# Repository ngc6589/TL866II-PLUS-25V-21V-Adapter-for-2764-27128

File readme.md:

# TL866II PLUS 25V/21V アダプター for 2764/17128

## 概要
当アダプタは XGecu TL866II PLUS プログラマにて 2764/27128 UV-EPROM 書き込みのための 25V/21V を供給するサポートアダプターです。TL866II PLUS の書き込み電圧 18V を検出すると ROM の VPP ピンに 25V/21V を供給します。25V/21V の電圧は  9～12V の ACアダプタから供給された電圧を昇圧ICで 25V/21V にします。

基板は https://www.em9system.com/?p=989 にて頒布いたします。

## 部品表
本来は部品の種類別にソートするものですが、購入先別に分けて記載しています。

|部品番号|部品名|URL|数量|備考|
|----|----|----|----|----|
|U1|DCDCコンバーター制御用IC NJM2360AD|https://akizukidenshi.com/catalog/g/gI-12365/|1|MC34063A も使えます|
|U1|丸ピンICソケット ( 8P)|https://akizukidenshi.com/catalog/g/gP-00035/|1|
|Q1|トランジスタ 2SA733L-K-T92-K 60V150mA|https://akizukidenshi.com/catalog/g/gI-11427/|1|TO-92ECB 手持ちの 2SA1015 などもOK|
|Q2|トランジスタ 2SC945L-K-T92-K 60V150mA|https://akizukidenshi.com/catalog/g/gI-11428/|1|TO-92ECB 手持ちの 2SC1815 などもOK|
|D1,D3|ショットキーバリアダイオード 40V1A 11EQS04|https://akizukidenshi.com/catalog/g/gI-11363/|2|
|D2|定電圧ダイオード(ツェナーダイオード) 15V500mW GDZJ15C|https://akizukidenshi.com/catalog/g/gI-07498/|1|DO-34|
|C5|メタライズドポリエステルフィルムコンデンサ 1500pF100V|https://akizukidenshi.com/catalog/g/gP-14588/|1||7.5mm×6.5mm×2.5mm ピッチ5mm|
|L1|インダクター 220μH0.75A SRC1013|https://akizukidenshi.com/catalog/g/gP-16012/|1|11x12.5 ピッチ5mm|
|J1|2.1mm標準DCジャック(4A) 基板取付用 MJ-179PH|https://akizukidenshi.com/catalog/g/gC-06568/|1|
|J2|細ピンヘッダ 1×40 (黒)|https://akizukidenshi.com/catalog/g/gC-06631/|1|
|J3|ゼロプレッシャーICソケット 28P 600mil|https://akizukidenshi.com/catalog/g/gP-11743/|1|
|JP1|ジャンパーピン赤(2.54mmピッチ)(25個入)|https://akizukidenshi.com/catalog/g/gP-03688/|1|
|R1|小形金属皮膜抵抗(MOSX)2W 0.22Ω【MOSX2CR22J】 |https://www.marutsu.co.jp/pc/i/18085/|1|L=15mm D=4mm|
|R2|【MOS2C181J】小型酸金抵抗(MOS)2W 180Ω|https://www.marutsu.co.jp/pc/i/18155/|1|L=15mm D=4mm|
|R3|1/4W金属皮膜抵抗 4.7kΩ 黄紫黒茶茶【MF1/4CC4701F】 |https://www.marutsu.co.jp/pc/i/1313/|1|L=7.1mm D=2.3mm|
|R4|1/4W金属皮膜抵抗 24kΩ 赤黄黒赤茶【MF1/4CC2402F】 |https://www.marutsu.co.jp/pc/i/1283/|1|L=7.1mm D=2.3mm|
|R5|1/4W金属皮膜抵抗 1.5kΩ 茶緑黒茶茶【MF1/4CC1501F】|https://www.marutsu.co.jp/pc/i/1248/|1|L=7.1mm D=2.3mm|
|R6,R8,R9|1/4W金属皮膜抵抗 1kΩ 茶黒黒茶茶【MF1/4CC1001F】|https://www.marutsu.co.jp/pc/i/1263/|3|L=7.1mm D=2.3mm|
|R7|1/4W金属皮膜抵抗 12kΩ 茶赤黒赤茶【MF1/4CC1202F】|https://www.marutsu.co.jp/pc/i/1253/|1|L=7.1mm D=2.3mm|
|R10|1/4W金属皮膜抵抗 10kΩ 茶黒黒赤茶【MF1/4CC1002F】|https://www.marutsu.co.jp/pc/i/1251/|1|L=7.1mm D=2.3mm|
|C1,C3|【RDER71H104K0K1H03B】セラミックコンデンサ 0.1UF 50V X7R ラジアル|https://www.marutsu.co.jp/pc/i/834991/|2|4mmx2.5mm ピッチ5mm|
|C2|小形アルミニウム電解コンデンサー25V 100μF【25PK100MEFC】|https://www.marutsu.co.jp/pc/i/132144/|1|D=5mm ピッチ2mm|
|C4|小形アルミニウム電解コンデンサー50V 330μF【50PK330MEFC】|https://www.marutsu.co.jp/pc/i/132162/|1|D=10 ピッチ5mm|
|JP1|2ピン基板用ピンヘッダー[2ピン×1列]【2130S1*2GSE】 |https://www.marutsu.co.jp/pc/i/590531/|1|
||プリント基板||1|頒布品を買われた方は基板製造不要|

- R1, R2 は 2W サイズと大きいものを選定していますが、ROM のプログラミングだけでこのワット数は不要です。しかしながらこの回路を参考にされて電流を取り出す用途に流用された時は、発熱の可能性があるためマージンを取った形にしています。
- Q1, Q2 汎用でいいのですが、秋月だと10個単位とかになってしまうので1個単位で買えるトランジスタを選定しています。
- 1/4W 抵抗のうち、R3, R4, R5 は DC/DC チップの基準電圧用なので金属皮膜 1% を使用して下さい。それ以外の抵抗は 5% カーボンでも問題ありません。これも通販だと 10本/100本単位がほとんどなので1本単位で購入出来るものにしています。

部品表には書いていませんが、9～12V の ACアダプタもご用意ください。

## 回路図
リポジトリにある schematic-nnnnnn.pdf (nnnnnnは日付) を参照下さい。

## ガーバーファイル
リポジトリにある gaeber-nnnnnn.zip (nnnnnnは日付) を参照下さい。

## 組み立て時の注意
**ZIF ソケットをハンダ付けする前に細ピンヘッダを先にハンダ付けしてください。** これ以外は特に取り付け順はありません。

## 書き込み実績
手持ちが少ないですが以下の ROM 書き込み出来ました。
- INTEL D2764D(21V)
- FUJITSU MBM2764-25(21V)
- INTEL D27128-3(21V)
- FUJITSU MBM27128-20(21V)
- MITSUBISHI M5L27128K(21V)

## 書き込み方法
- アダプタを TL866II PLUS のソケットに装着する
- ROM の書き込み電圧に合わせて 25V はジャンパを外す 21V ならジャンパ装着する
- 9 ～ 12V の ACアダプタを挿して電源を供給する
- XGpro アプリケーションを起動しチップの選択をします。
- 画面左下の [Pin Detect] [Check ID] のチェックボックスを外す

- READ ボタンを押してエラーないことを確認
- HEX ファイルを LOAD する
- PROG ボタンを押して書き込む
- 書き込み不調の場合は Pulse Delay を最大 1000us にするといけることがあります。

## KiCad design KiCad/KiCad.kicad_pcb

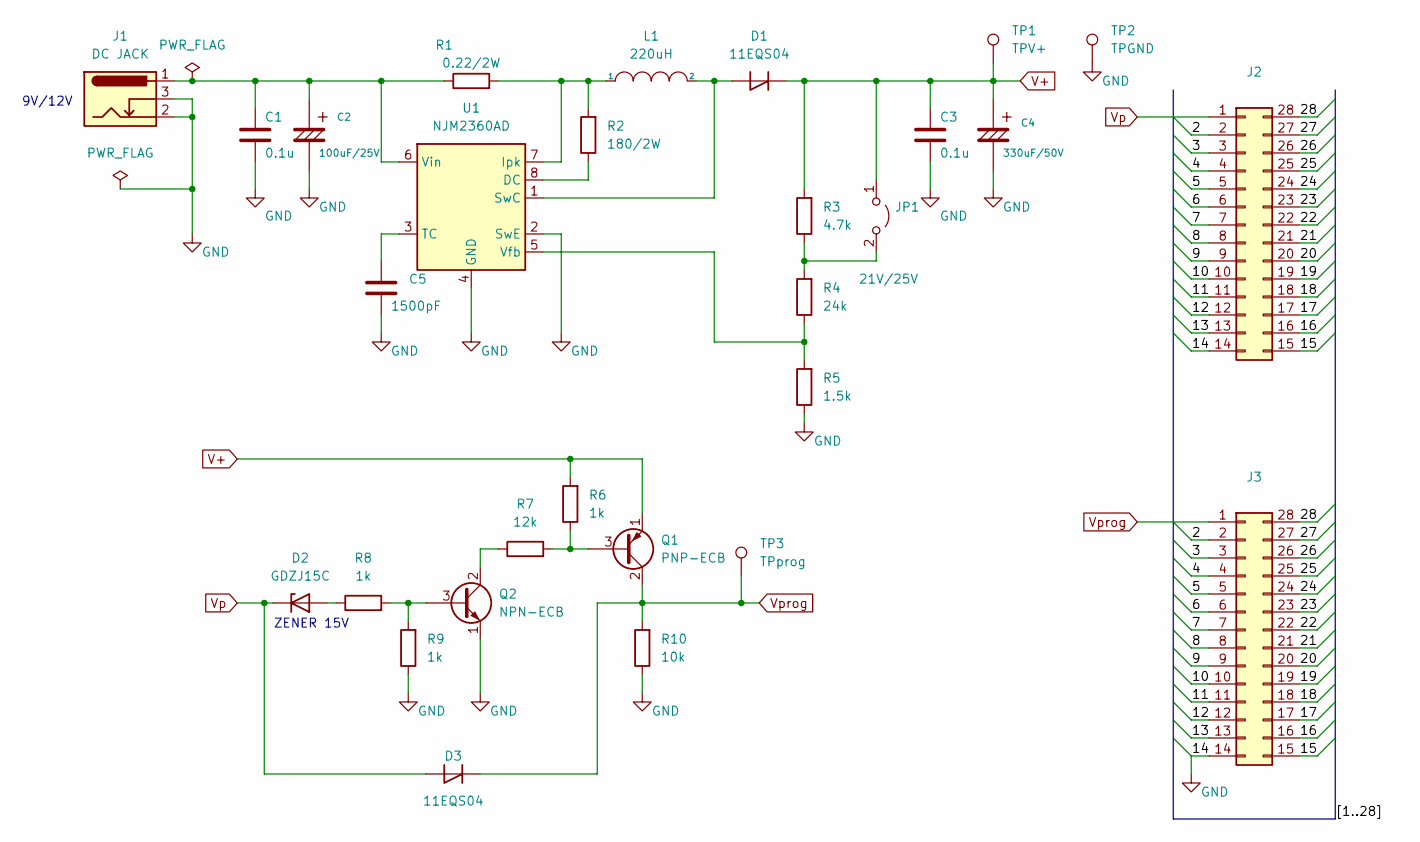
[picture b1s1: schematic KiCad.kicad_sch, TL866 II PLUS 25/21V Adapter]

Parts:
C1, C3: 0.1u; C_Disc_D4.7mm_W2.5mm_P5.00mm
C2: 100uF/25V; CP_Radial_D5.0mm_P2.00mm
C4: 330uF/50V; CP_Radial_D10.0mm_P5.00mm
C5: 1500pF; C_Rect_L7.2mm_W2.5mm_P5.00mm_FKS2_FKP2_MKS2_MKP2
D1, D3: 11EQS04; D_DO-41_SOD81_P10.16mm_Horizontal
D2: GDZJ15C; D_DO-34_SOD68_P7.62mm_Horizontal
J1: DC JACK; MJ-179PH
J2, J3: (no value)
JP1: 21V/25V; PinHeader_1x02_P2.54mm_Vertical
L1: 220uH; L_Radial_D12.0mm_P5.00mm_Fastron_11P
Q1: PNP-ECB; TO-92
Q2: NPN-ECB; TO-92
R1: 0.22/2W; R_Axial_DIN0414_L11.9mm_D4.5mm_P15.24mm_Horizontal
R2: 180/2W; R_Axial_DIN0414_L11.9mm_D4.5mm_P15.24mm_Horizontal
R3: 4.7k; R_Axial_DIN0207_L6.3mm_D2.5mm_P7.62mm_Horizontal
R4: 24k; R_Axial_DIN0207_L6.3mm_D2.5mm_P7.62mm_Horizontal
R5: 1.5k; R_Axial_DIN0207_L6.3mm_D2.5mm_P7.62mm_Horizontal
R6, R8, R9: 1k; R_Axial_DIN0207_L6.3mm_D2.5mm_P7.62mm_Horizontal
R7: 12k; R_Axial_DIN0207_L6.3mm_D2.5mm_P7.62mm_Horizontal
R10: 10k; R_Axial_DIN0207_L6.3mm_D2.5mm_P7.62mm_Horizontal
TP1: TPV+; TestPoint_THTPad_D2.0mm_Drill1.0mm
TP2: TPGND; TestPoint_THTPad_D2.0mm_Drill1.0mm
TP3: TPprog; TestPoint_THTPad_D2.0mm_Drill1.0mm
U1: NJM2360AD; DIP-8_W7.62mm

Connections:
/2: J2.2, J3.2
/3: J2.3, J3.3
/4: J2.4, J3.4
/5: J2.5, J3.5
/6: J2.6, J3.6
/7: J2.7, J3.7
/8: J2.8, J3.8
/9: J2.9, J3.9
/10: J2.10, J3.10
/11: J2.11, J3.11
/12: J2.12, J3.12
/13: J2.13, J3.13
/15: J2.15, J3.15
/16: J2.16, J3.16
/17: J2.17, J3.17
/18: J2.18, J3.18
/19: J2.19, J3.19
/20: J2.20, J3.20
/21: J2.21, J3.21
/22: J2.22, J3.22
/23: J2.23, J3.23
/24: J2.24, J3.24
/25: J2.25, J3.25
/26: J2.26, J3.26
/27: J2.27, J3.27
/28: J2.28, J3.28
GND: C1.2, C2.2, C3.2, C4.2, C5.2, J1.2, J1.3, J2.14, J3.14, Q2.1 (E), R5.1, R9.1, R10.1, TP2.1, U1.2 (SwE), U1.4 (GND)
unnamed: C1.1, C2.1, J1.1, R1.1, U1.6 (Vin)
unnamed: C5.1, U1.3 (TC)
unnamed: D1.2 (A), L1.2, U1.1 (SwC)
unnamed: D2.2 (A), R8.1
unnamed: JP1.2 (B), R3.1, R4.2
unnamed: L1.1, R1.2, R2.2, U1.7 (Ipk)
unnamed: Q1.3 (B), R6.1, R7.2
unnamed: Q2.2 (C), R7.1
unnamed: Q2.3 (B), R8.2, R9.2
unnamed: R2.1, U1.8 (DC)
unnamed: R4.1, R5.2, U1.5 (Vfb)
V+: C3.1, C4.1, D1.1 (K), JP1.1 (A), Q1.1 (E), R3.2, R6.2, TP1.1
Vp: D2.1 (K), D3.2 (A), J2.1
Vprog: D3.1 (K), J3.1, Q1.2 (C), R10.2, TP3.1

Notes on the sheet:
ZENER 15V
9V/12V

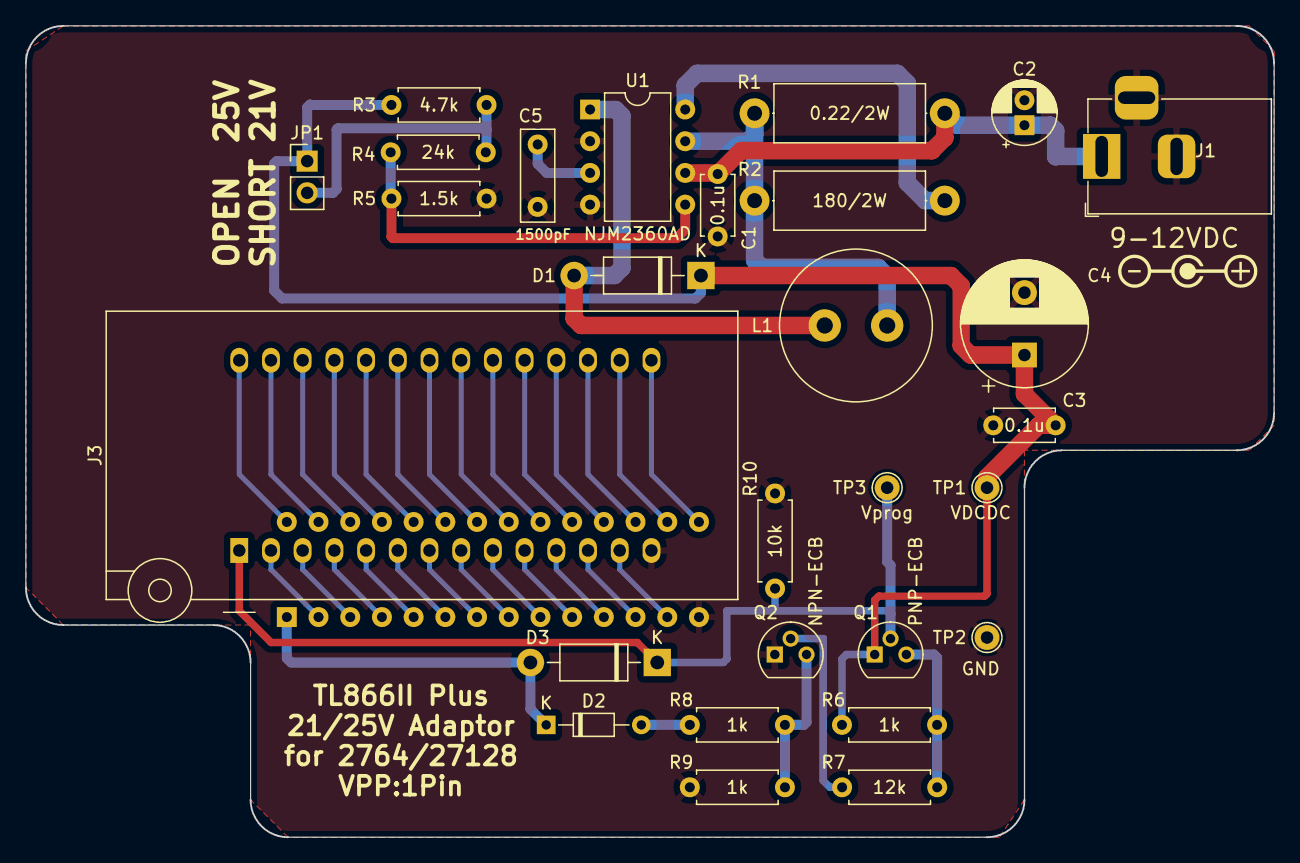
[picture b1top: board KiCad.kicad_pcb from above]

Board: 2 copper layers, 100.0 x 65.0 mm, 29 parts (0 on the bottom side), 41 nets.

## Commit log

2022-05-07 add readme.md
2022-05-07 add LICENSE
2022-05-07 add schmatic
2022-05-07 update readme.md and Material folder
2022-05-07 add schematic and gerber file
2022-05-07 add kicad folder
2022-06-20 add .gitignore
2023-03-19 Q1 PNP トランジスタの商品ページ URL を更新
